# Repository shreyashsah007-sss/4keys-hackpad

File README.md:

# 4-Key Hackpad Project

## 1. Overall Hackpad
Here is the finished design of my custom macro pad.

## 2. Bill of Materials (BOM)

| Component | Quantity | Description |
| :--- | :--- | :--- |
| **Microcontroller** | 1 | Seeed Studio XIAO RP2040 |
| **Switches** | 4 | Cherry MX Style Switches |
| **LEDs** | 2 | SK6812 MINI (3.5x3.5mm) |
| **Rotary Encoder** | 1 | Alps EC11E Rotary Encoder |
| **Keycaps** | 4 | 1u Keycaps (MX Compatible) |
| **Knob** | 1 | Rotary Encoder Knob |
| **PCB** | 1 | Custom Hackpad PCB |
| **Case** | 1 | 3D Printed Case |
| **Screws** | 4 | M3x16mm Screws |
| **Inserts** | 4 | M3x5mmx4mm Heatset Inserts |
| **Wire** | - |
[BOM.csv](https://github.com/user-attachments/files/24127032/BOM.csv)

## 3. CAD Assembly (How it fits)
The case consists of a top and bottom shell, screwed together.

## 4. Electronics
### Schematic
The wiring logic for the switches and microcontroller.

### PCB Design
The physical board layout designed in KiCad.

## 5. Firmware
[main.py](https://github.com/user-attachments/files/24104565/main.py)

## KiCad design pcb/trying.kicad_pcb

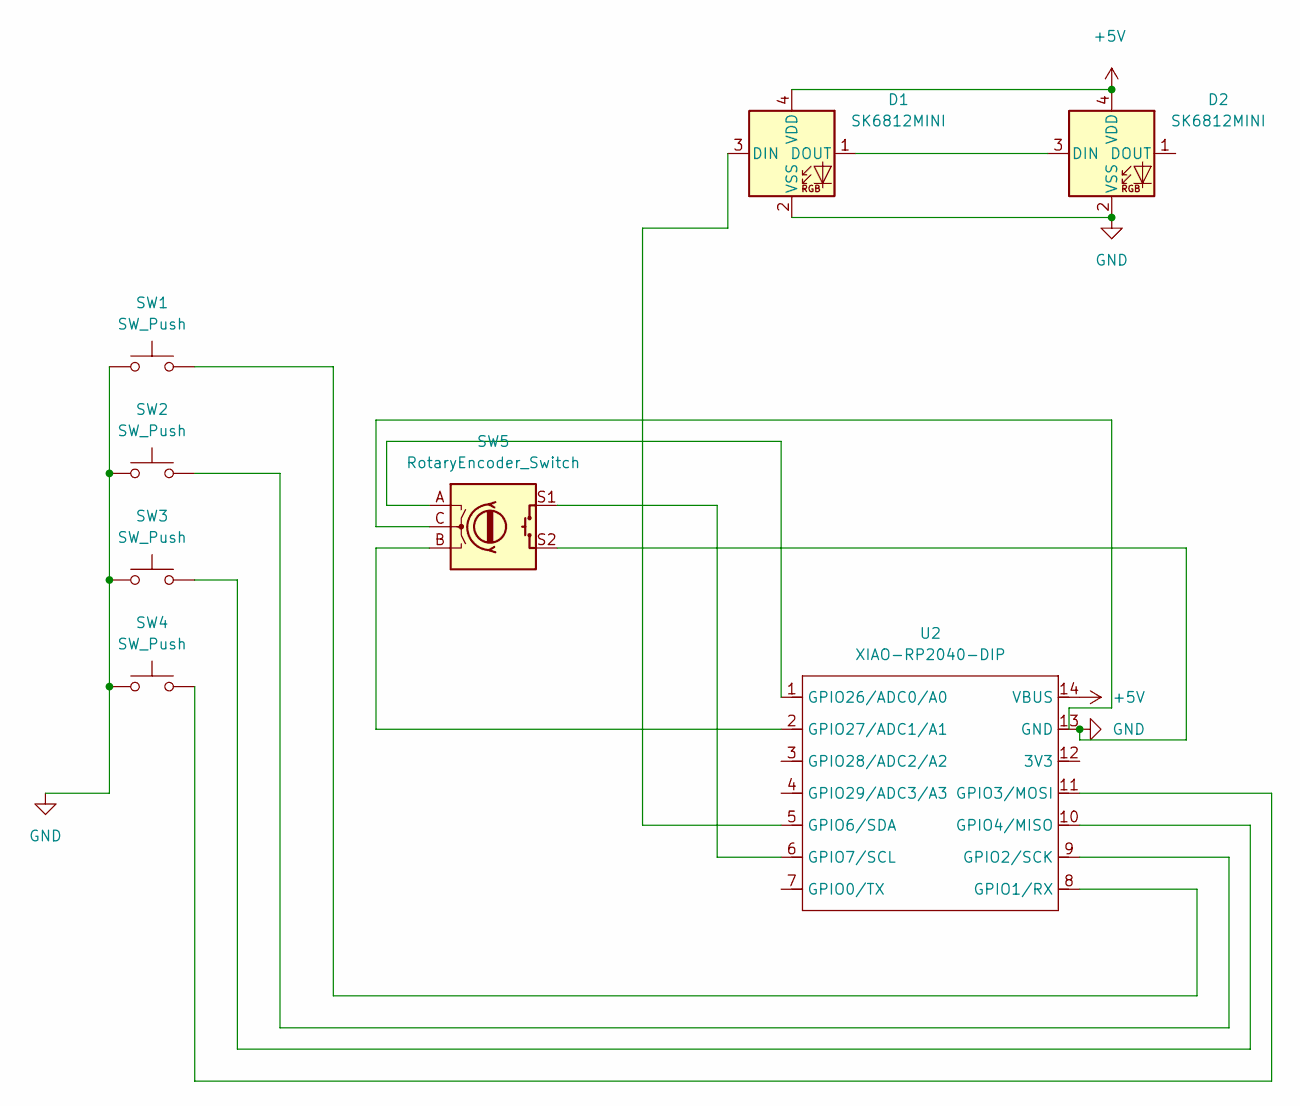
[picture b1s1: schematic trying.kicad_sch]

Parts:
D1, D2: SK6812MINI; LED_SK6812MINI_PLCC4_3.5x3.5mm_P1.75mm
SW1, SW2, SW3, SW4: SW_Push; SW_Cherry_MX_1.00u_PCB
SW5: RotaryEncoder_Switch; RotaryEncoder_Alps_EC11E-Switch_Vertical_H20mm
U2: XIAO-RP2040-DIP

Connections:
+5V: D1.4 (VDD), D2.4 (VDD), U2.14 (VBUS)
GND: D1.2 (VSS), D2.2 (VSS), SW1.1, SW2.1, SW3.1, SW4.1, SW5.S2, U2.13 (GND)
unnamed: D1.3 (DIN), U2.5 (GPIO6/SDA)
unnamed: D1.1 (DOUT), D2.3 (DIN)
unnamed: SW1.2, U2.8 (GPIO1/RX)
unnamed: SW2.2, U2.9 (GPIO2/SCK)
unnamed: SW4.2, U2.11 (GPIO3/MOSI)
unnamed: SW3.2, U2.10 (GPIO4/MISO)
unnamed: SW5.S1, U2.6 (GPIO7/SCL)
unnamed: SW5.A, U2.1 (GPIO26/ADC0/A0)
unnamed: SW5.B, U2.2 (GPIO27/ADC1/A1)

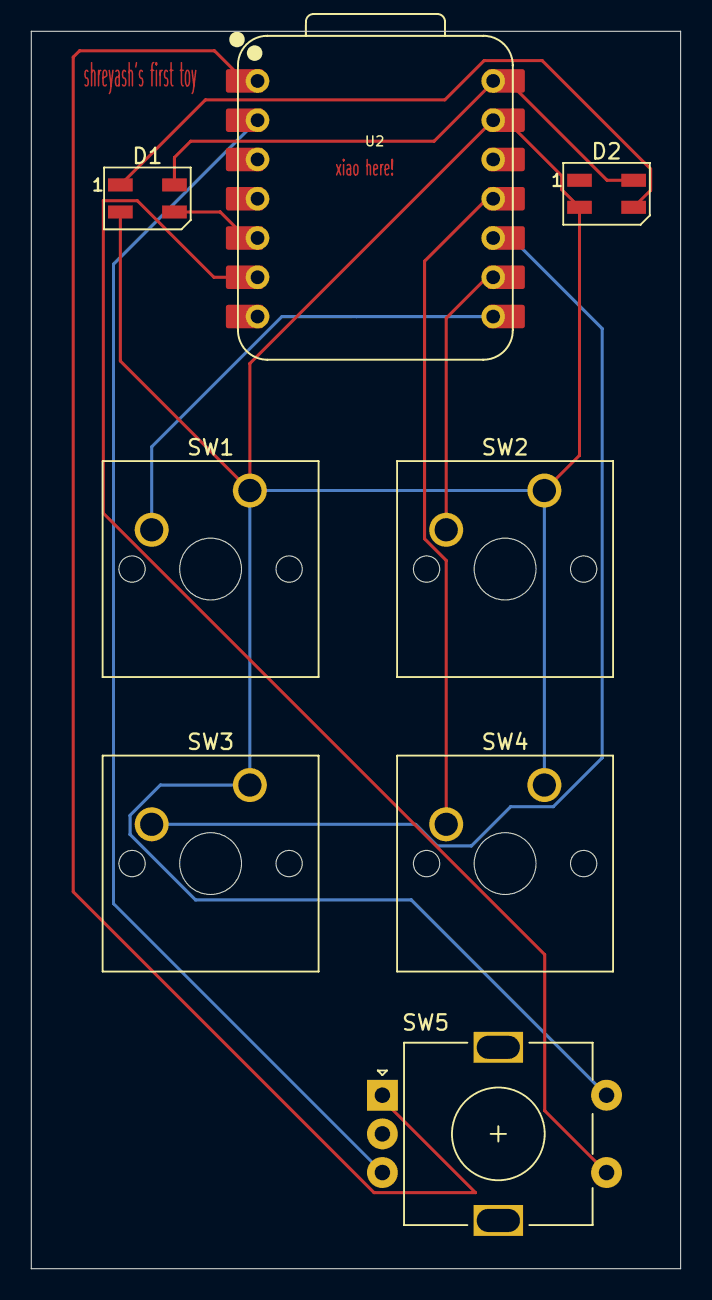
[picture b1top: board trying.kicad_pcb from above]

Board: 2 copper layers, 42.0 x 80.0 mm, 8 parts (0 on the bottom side), 11 nets.
